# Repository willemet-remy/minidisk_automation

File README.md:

# Wireless water-level logger for tension infiltrometers

**Slimme Minidisk** s a wireless data logger designed to measure the distance to the water surface inside a reservoir. 

The Slimme Minidisk was conceptualized to improve the accuracy and efficiency of soil infiltration measurements while allowing a greater number of replicates to be performed within the same timeframe. Instead of manually timing water-level drops with a stopwatch and reading the meniscus by eye, a 3D-printed cap mounted on top of the reservoir measures the distance to the water surface using a Time-of-Flight (ToF) laser sensor (ST VL53L4CD). The measurements are then transmitted wirelessly to a laptop, enabling automated data collection. This reduces the time and effort required for each measurement and allows multiple infiltrometers to be monitored simultaneously, increasing the number of replicates that can be performed at the same time.

In this example, the device was developed for an infiltrometer similar to the [METER Mini Disk Infiltrometers](https://www.metergroup.com/), with one key difference: the Mariotte bottle is positioned alongside the mini disk rather than being integrated into it. However, the concept can be adapted to other devices that require water-level monitoring.

A single USB receiver can communicate with multiple infiltrometers simultaneously via ESP-NOW (2.4 GHz), without requiring a Wi-Fi network or device pairing. This makes the system suitable for conducting parallel measurements with multiple tension infiltrometers in a field plot.

The system is designed to support up to 20 registered peers; however, this maximum capacity has not yet been experimentally validated.

| System overview | Sensor cap interior |
| :---: | :---: |
|  |  |

## How it works

Each sensor cap houses an **ESP32-C3 Mini**, a **VL53L4CD** distance sensor pointing down the reservoir tube, an **18650 Li-ion battery** with USB charging, a power switch, a push button, and a small buzzer:

- **1 Hz averaged readings**: The sensor samples continuously (~20 readings/s) and broadcasts one averaged water-level distance (`mm`) per second.
- **Drop-free wireless link**: Every radio packet carries the last 5 seconds of measurements, so the receiver automatically fills in missed packets if the signal briefly drops.
- **Button control in the field**: Once a session is open on the laptop, you can walk out, place each infiltrometer on the soil, and start or stop recording directly on the cap by **holding its button for 2 seconds**:
  - **1 short beep** on power-up (followed by a long beep if the VL53L4CD sensor is not detected)
  - **2 beeps** when recording starts
  - **3 beeps** when recording stops

## Hardware & wiring

| ESP32-C3 Pin | Connected part | Notes |
| :--- | :--- | :--- |
| `3.3V` / `GND` | VL53L4CD power, buzzer `-`, button | Regulated 3.3 V supply and common ground |
| `GPIO 8` | VL53L4CD `SDA` | I2C data (400 kHz) |
| `GPIO 9` | VL53L4CD `SCL` | I2C clock |
| `GPIO 6` | VL53L4CD `XSHUT` | Sensor enable |
| `GPIO 1` | Active buzzer `+` | Status beeps |
| `GPIO 2` | Push button to `GND` | Internal pull-up (`INPUT_PULLUP`), hold 2 s to toggle |

CAD models and ready-to-print STL/3MF enclosures are in [`Model/`](Model/), and KiCad PCB files are in [`PCB_microcontroller/`](PCB_microcontroller/).

## Flashing the firmware

The firmware in [`src/Esp32/`](src/Esp32/) is built with [PlatformIO](https://platformio.org/). Pre-configured environments in [`platformio.ini`](src/Esp32/platformio.ini) set the board type and `NODE_ID` automatically, so you do not need to edit `config.h` between boards:

```powershell
cd src/Esp32

# USB receiver (use receiver_s3 instead if your receiver is an ESP32-S3 DevKit)
pio run -e receiver -t upload

# Sensor nodes (each node needs a distinct ID)
pio run -e node1 -t upload   # MINIDISK_01
pio run -e node2 -t upload   # MINIDISK_02
```

Environments up to `node4` are included out of the box; copy one in `platformio.ini` if you add more sensors. For bench testing over USB serial (`115200` baud), a node accepts `STATUS`, `START`, `STOP`, and `BEEP`.

## Desktop app & field workflow

Install Python 3.9+ along with `pyserial` and `matplotlib`, then run the acquisition interface:

```powershell
python -m pip install pyserial matplotlib
python src/Computer/minidisk_acquisition.py
```

1. **Connect the receiver**: Plug in the USB receiver, pick its serial port, and click **Connect**. A green status indicator confirms the receiver heartbeat, and powered-on nodes appear automatically with their live distance and link quality.
2. **Open a session**: Click **New session…** and enter the campaign name, plot/location, optional operator/notes, and output folder (previous campaign names, operator, and folder are saved for next time).
3. **Record in the field**: Hold the button on a sensor for **2 seconds** (2 beeps) when the infiltrometer makes contact with the soil, or start it remotely from the laptop. Any sensor started with its button during an open session is added to the window automatically.
4. **Track suction tension**: Select the applied suction (`0` to `10 cm`, in `1 cm` steps) on each sensor's card. Changing the tension during a measurement updates the CSV immediately and marks the change on the live infiltration curve.
5. **Stop or refill**: Hold the button for **2 seconds** (3 beeps) to stop. Starting again on the same spot increments the `run` counter and begins a fresh curve while keeping all runs in the same session CSV.

## CSV output

Data is written live to `{campaign}_{location}_{YYYYMMDD_HHMM}.csv` (by default in `~/Documents/SlimmeMinidisk/`) while a node is recording. Each row logs:

`pc_time`, `campaign`, `location`, `operator`, `notes`, `sensor_name`, `node_id`, `run`, `seq`, `time_s`, `distance_mm`, `valid`, `range_status`, `n_avg`, `tension_cm`

## Repository layout

- [`Figures/`](Figures/) — System schematic and hardware photos
- [`Model/`](Model/) — Fusion 360 files and 3D-printable enclosures
- [`PCB_microcontroller/`](PCB_microcontroller/) — KiCad schematics, PCB layouts, and BOM
- [`src/Esp32/`](src/Esp32/) — ESP32-C3 / ESP32-S3 node and receiver firmware
- [`src/Computer/`](src/Computer/) — Python desktop acquisition app (`minidisk_acquisition.py`)

## Authors

- **Rémy Willemet** – *ILVO / Ghent University* – [remy.willemet@ilvo.vlaanderen.be](mailto:remy.willemet@ilvo.vlaanderen.be)

## License

This project utilizes separate licensing for hardware designs and software:

- **Hardware Designs** (`hardware/`): Licensed under the **[CERN Open Hardware Licence Version 2 - Permissive (CERN-OHL-P v2)](LICENSE)**.
  - Copyright © 2026 **Rémy Willemet**.
- **Software & Firmware** (`firmware/`, `software/`, companion scripts): Dedicated to the **Public Domain** under **[Creative Commons CC0 1.0 Universal](LICENSE)** (or The Unlicense) with no copyright reserved.

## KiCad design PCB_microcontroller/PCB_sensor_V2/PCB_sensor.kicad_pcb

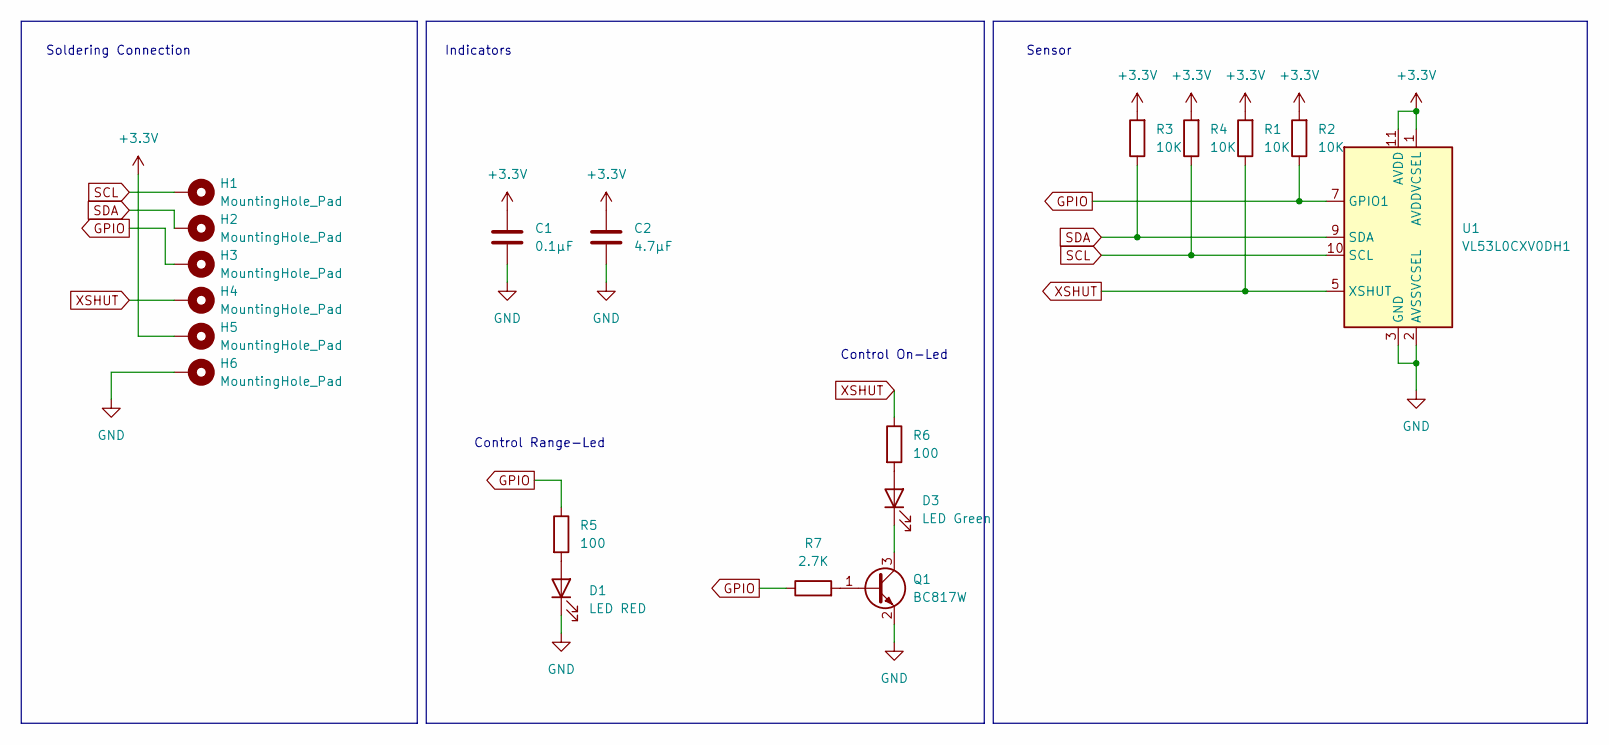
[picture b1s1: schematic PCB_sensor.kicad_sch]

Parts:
C1: 0.1µF; C_0201_0603Metric_Pad0.64x0.40mm_HandSolder
C2: 4.7µF; C_0201_0603Metric_Pad0.64x0.40mm_HandSolder
D1: LED RED; LED_0201_0603Metric_Pad0.64x0.40mm_HandSolder
D3: LED Green; LED_0201_0603Metric_Pad0.64x0.40mm_HandSolder
H1: MountingHole_Pad; TestPoint_Pad_1.5x1.5mm
H2, H3, H4, H5, H6: MountingHole_Pad; TestPoint_Pad_D1.5mm
Q1: BC817W; SOT-323_SC-70
R1, R2, R3, R4: 10K; R_0201_0603Metric_Pad0.64x0.40mm_HandSolder
R5, R6: 100; R_0201_0603Metric_Pad0.64x0.40mm_HandSolder
R7: 2.7K; R_0201_0603Metric_Pad0.64x0.40mm_HandSolder
U1: VL53L0CXV0DH1; ST_VL53L1x

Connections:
+3.3V: C1.1, C2.1, H5.1, R1.2, R2.2, R3.2, R4.2, U1.1 (AVDDVCSEL), U1.11 (AVDD)
GND: C1.2, C2.2, D1.1 (K), H6.1, Q1.2 (E), U1.2 (AVSSVCSEL), U1.3 (GND), U1.4 (GND), U1.6 (GND), U1.12 (GND)
GPIO: H3.1, R2.1, R5.1, R7.1, U1.7 (GPIO1)
unnamed: D1.2 (A), R5.2
unnamed: D3.2 (A), R6.2
unnamed: D3.1 (K), Q1.3 (C)
unnamed: Q1.1 (B), R7.2
SCL: H1.1, R4.1, U1.10 (SCL)
SDA: H2.1, R3.1, U1.9 (SDA)
XSHUT: H4.1, R1.1, R6.1, U1.5 (XSHUT)

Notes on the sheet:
Indicators
Control On-Led
Sensor
Soldering Connection
Control Range-Led

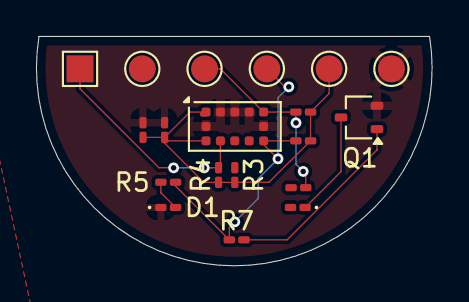
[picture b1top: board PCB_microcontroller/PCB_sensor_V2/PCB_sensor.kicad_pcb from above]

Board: 2 copper layers, 22.0 x 12.7 mm, 19 parts (0 on the bottom side), 10 nets.

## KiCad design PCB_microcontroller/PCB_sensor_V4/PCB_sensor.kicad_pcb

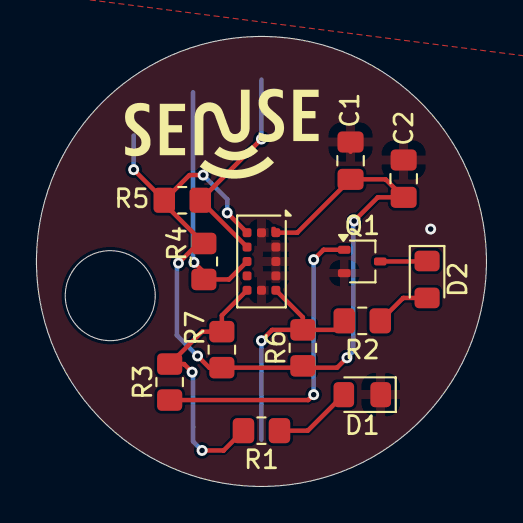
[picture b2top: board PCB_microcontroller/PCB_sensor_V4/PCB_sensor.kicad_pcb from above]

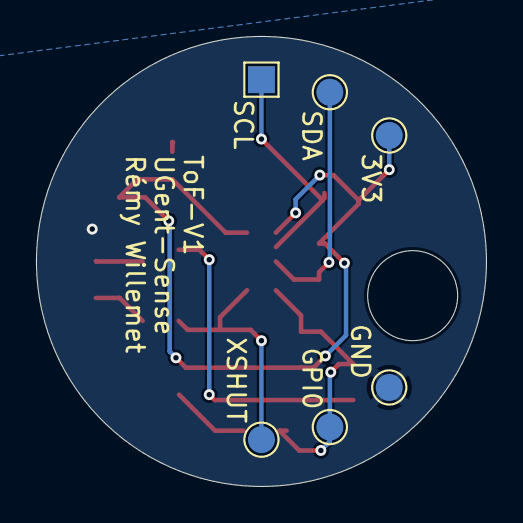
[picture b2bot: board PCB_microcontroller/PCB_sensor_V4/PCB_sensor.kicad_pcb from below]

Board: 2 copper layers, 25.0 x 25.0 mm, 20 parts (6 on the bottom side), 10 nets.

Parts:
C1: 0.1µF; C_0805_2012Metric_Pad1.18x1.45mm_HandSolder
C2: 4.7µF; C_0805_2012Metric_Pad1.18x1.45mm_HandSolder
D1: LED RED; LED_0805_2012Metric_Pad1.15x1.40mm_HandSolder
D2: LED Green; LED_0805_2012Metric_Pad1.15x1.40mm_HandSolder
GND: GND; TestPoint_Pad_D1.5mm
H1: SCL; TestPoint_Pad_1.5x1.5mm
H2: SDA; TestPoint_Pad_D1.5mm
H3: GPI0; TestPoint_Pad_D1.5mm
H4: XSHUT; TestPoint_Pad_D1.5mm
H5: 3V3; TestPoint_Pad_D1.5mm
H7: MountingHole_Pad; MountingHole_5mm_modif
Q1: BC817W; SOT-323_SC-70
R1, R2: 100; R_0805_2012Metric_Pad1.20x1.40mm_HandSolder
R3: 2.7K; R_0805_2012Metric_Pad1.20x1.40mm_HandSolder
R4: 10KΩ; R_0805_2012Metric_Pad1.20x1.40mm_HandSolder
R5, R6, R7: 10K; R_0805_2012Metric_Pad1.20x1.40mm_HandSolder
U1: VL53L0CXV0DH1; ST_VL53L1x

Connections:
+3.3V: C1.1, C2.1, H5.1, R4.2, R5.2, R6.2, R7.2, U1.1 (AVDDVCSEL), U1.11 (AVDD)
GND: C1.2, C2.2, D1.1 (K), GND.1, Q1.2 (E), U1.2 (AVSSVCSEL), U1.3 (GND), U1.4 (GND), U1.6 (GND), U1.12 (GND)
GPIO: H3.1, R1.1, R3.1, R7.1, U1.7 (GPIO1)
unnamed: D1.2 (A), R1.2
unnamed: D2.2 (A), R2.2
unnamed: D2.1 (K), Q1.3 (C)
unnamed: Q1.1 (B), R3.2
SCL: H1.1, R5.1, U1.10 (SCL)
SDA: H2.1, R4.1, U1.9 (SDA)
XSHUT: H4.1, R2.1, R6.1, U1.5 (XSHUT)

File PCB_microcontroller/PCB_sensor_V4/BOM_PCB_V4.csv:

"Reference","Qty","Value","DNP","Exclude from BOM","Exclude from Board","Footprint","Datasheet"
"C1","1","0.1µF","","","","Capacitor_SMD:C_0805_2012Metric_Pad1.18x1.45mm_HandSolder","~"
"C2","1","4.7µF","","","","Capacitor_SMD:C_0805_2012Metric_Pad1.18x1.45mm_HandSolder","~"
"D1","1","LED RED","","","","LED_SMD:LED_0805_2012Metric_Pad1.15x1.40mm_HandSolder","~"
"D2","1","LED Green","","","","LED_SMD:LED_0805_2012Metric_Pad1.15x1.40mm_HandSolder","~"
"H1","1","SCL","","Excluded from BOM","","TestPoint:TestPoint_Pad_1.5x1.5mm","~"
"H2","1","SDA","","Excluded from BOM","","TestPoint:TestPoint_Pad_D1.5mm","~"
"H3","1","GPI0","","Excluded from BOM","","TestPoint:TestPoint_Pad_D1.5mm","~"
"H4","1","XSHUT","","Excluded from BOM","","TestPoint:TestPoint_Pad_D1.5mm","~"
"H5","1","3V3","","Excluded from BOM","","TestPoint:TestPoint_Pad_D1.5mm","~"
"H6","1","GND","","Excluded from BOM","","TestPoint:TestPoint_Pad_D1.5mm","~"
"H7","1","MountingHole_Pad","","Excluded from BOM","","Growing_chamber:MountingHole_5mm_modif","~"
"Q1","1","BC817W","","","","Package_TO_SOT_SMD:SOT-323_SC-70","https://www.onsemi.com/pub/Collateral/BC818-D.pdf"
"R1,R2","2","100","","","","Resistor_SMD:R_0805_2012Metric_Pad1.20x1.40mm_HandSolder","~"
"R3","1","2.7K","","","","Resistor_SMD:R_0805_2012Metric_Pad1.20x1.40mm_HandSolder","~"
"R4","1","10KΩ","","","","Resistor_SMD:R_0805_2012Metric_Pad1.20x1.40mm_HandSolder","~"
"R5,R6,R7","3","10K","","","","Resistor_SMD:R_0805_2012Metric_Pad1.20x1.40mm_HandSolder","~"
"U1","1","VL53L0CXV0DH1","","","","Sensor_Distance:ST_VL53L1x","https://www.st.com/resource/en/datasheet/vl53l0x.pdf"

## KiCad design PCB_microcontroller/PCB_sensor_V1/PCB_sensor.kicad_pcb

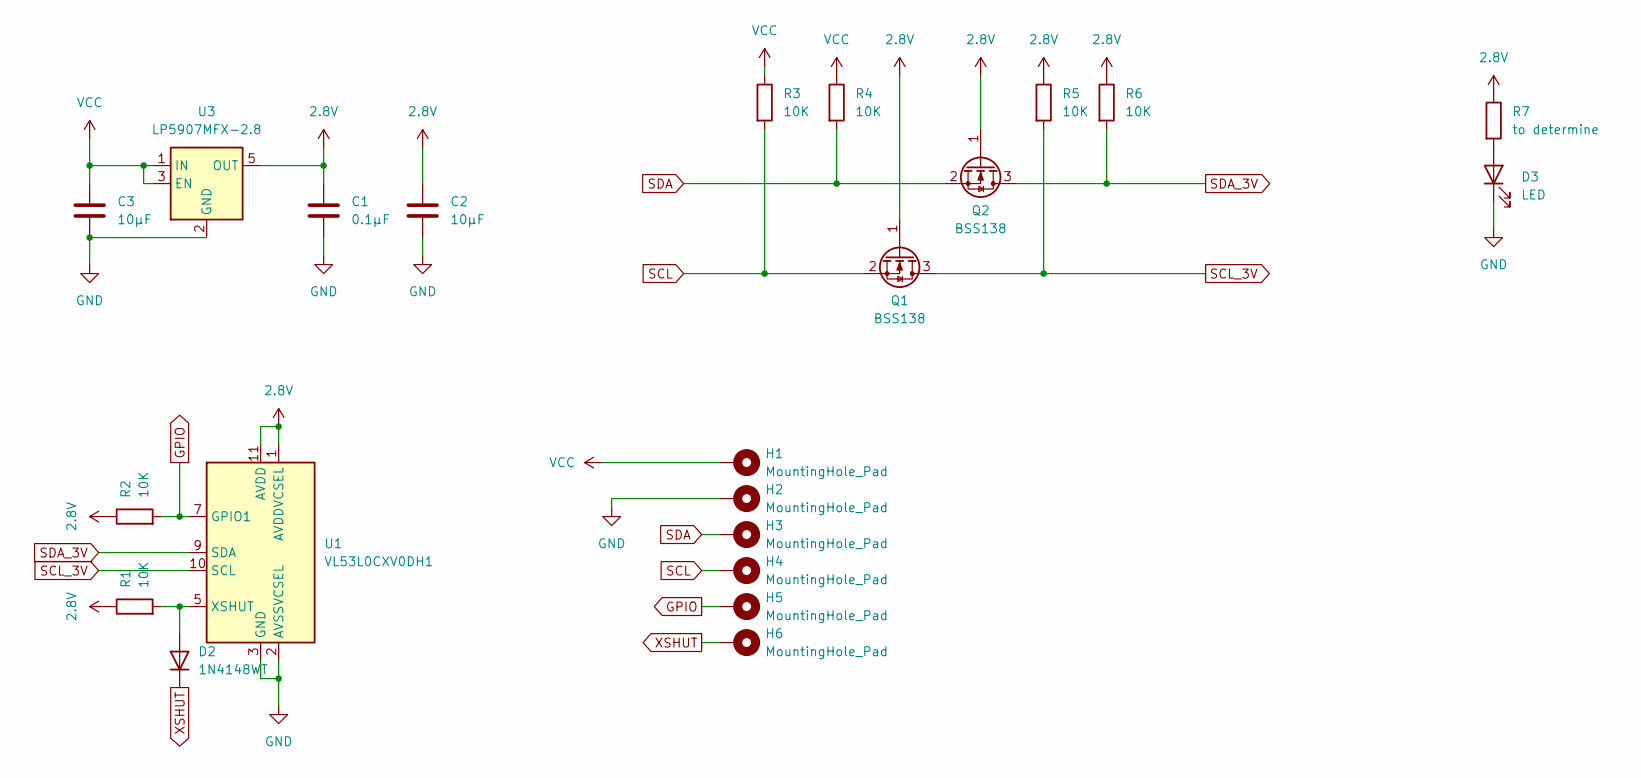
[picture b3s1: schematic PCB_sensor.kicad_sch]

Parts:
C1: 0.1µF; C_0201_0603Metric_Pad0.64x0.40mm_HandSolder
C2, C3: 10µF; C_0201_0603Metric_Pad0.64x0.40mm_HandSolder
D2: 1N4148WT; D_SOD-523
D3: LED; LED_0201_0603Metric_Pad0.64x0.40mm_HandSolder
H1: MountingHole_Pad; TestPoint_Pad_1.5x1.5mm
H2, H3, H4, H5, H6: MountingHole_Pad; TestPoint_Pad_D1.5mm
Q1, Q2: BSS138; SOT-23
R1, R2, R3, R4, R5, R6: 10K; R_0201_0603Metric_Pad0.64x0.40mm_HandSolder
R7: to determine; R_0201_0603Metric_Pad0.64x0.40mm_HandSolder
U1: VL53L0CXV0DH1; ST_VL53L1x
U3: LP5907MFX-2.8; SOT-23-5

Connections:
2.8V: C1.1, C2.1, Q1.1 (G), Q2.1 (G), R1.1, R2.1, R5.1, R6.1, R7.1, U1.1 (AVDDVCSEL), U1.11 (AVDD), U3.5 (OUT)
GND: C1.2, C2.2, C3.2, D3.1 (K), H2.1, U1.2 (AVSSVCSEL), U1.3 (GND), U1.4 (GND), U1.6 (GND), U1.12 (GND), U3.2 (GND)
GPIO: H5.1, R2.2, U1.7 (GPIO1)
unnamed: D2.2 (A), R1.2, U1.5 (XSHUT)
unnamed: D3.2 (A), R7.2
SCL: H4.1, Q1.2 (S), R3.2
SCL_3V: Q1.3 (D), R5.2, U1.10 (SCL)
SDA: H3.1, Q2.2 (S), R4.2
SDA_3V: Q2.3 (D), R6.2, U1.9 (SDA)
VCC: C3.1, H1.1, R3.1, R4.1, U3.1 (IN), U3.3 (EN)
XSHUT: D2.1 (K), H6.1

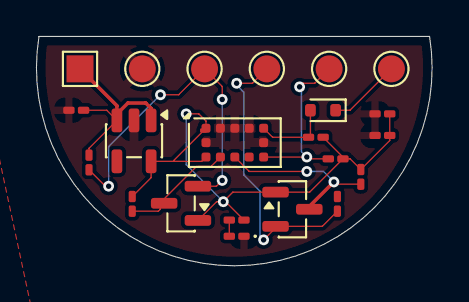
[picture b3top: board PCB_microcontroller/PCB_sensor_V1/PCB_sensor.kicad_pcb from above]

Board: 2 copper layers, 22.0 x 12.7 mm, 22 parts (0 on the bottom side), 11 nets.

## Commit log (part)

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2026-01-08 Hello World
2026-01-08 ReadMe Up to date
2026-01-08 ReadMe Up to date 2
2026-01-08 ReadMe Up to date 3
2026-01-09 Question about servo motors
2026-01-30 access hardware dvp files
2026-01-30 Work on prototype
2026-02-03 BOM creation
2026-02-12 Development lit/cap for mindisk
2026-02-12 Code for minidisk VL
2026-02-12 example added from github for multiple sensors
2026-02-13 Code V2 - not working
2026-02-13 I2C find but not able to make connection
2026-02-16 not working-search funciton might be the problem
2026-02-16 seems to work
2026-02-16 not working
2026-02-19 function from sparkfun working
2026-02-19 start Raspberrypi interface
2026-02-19 Printable caps
2026-02-23 modif gui interface
2026-02-27 Software V1-working
2026-03-01 modfic batterie
2026-03-01 steady flow algo
2026-03-02 modif code for adafruit
2026-03-02 Final version 3D parts
2026-03-02 FIxed last error
2026-03-03 Final version hardware
2026-03-05 new pieces top and joint
2026-03-07 add debugging parts
2026-03-08 case
2026-03-08 2nd part case
2026-03-09 Cap minidisk tpu
2026-03-09 case 2nd
2026-03-10 cap V2
2026-03-10 cap V3
2026-03-11 cap sensor
2026-03-11 cap sensor V2
2026-03-13 Modif cap
2026-03-13 Creation arduino version
2026-03-13 Last version software
2026-03-13 first version arduino reading
2026-03-13 Adruino V2
2026-03-13 Structure folder
2026-03-13 modif interface final

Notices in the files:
README.md:
License: MIT
